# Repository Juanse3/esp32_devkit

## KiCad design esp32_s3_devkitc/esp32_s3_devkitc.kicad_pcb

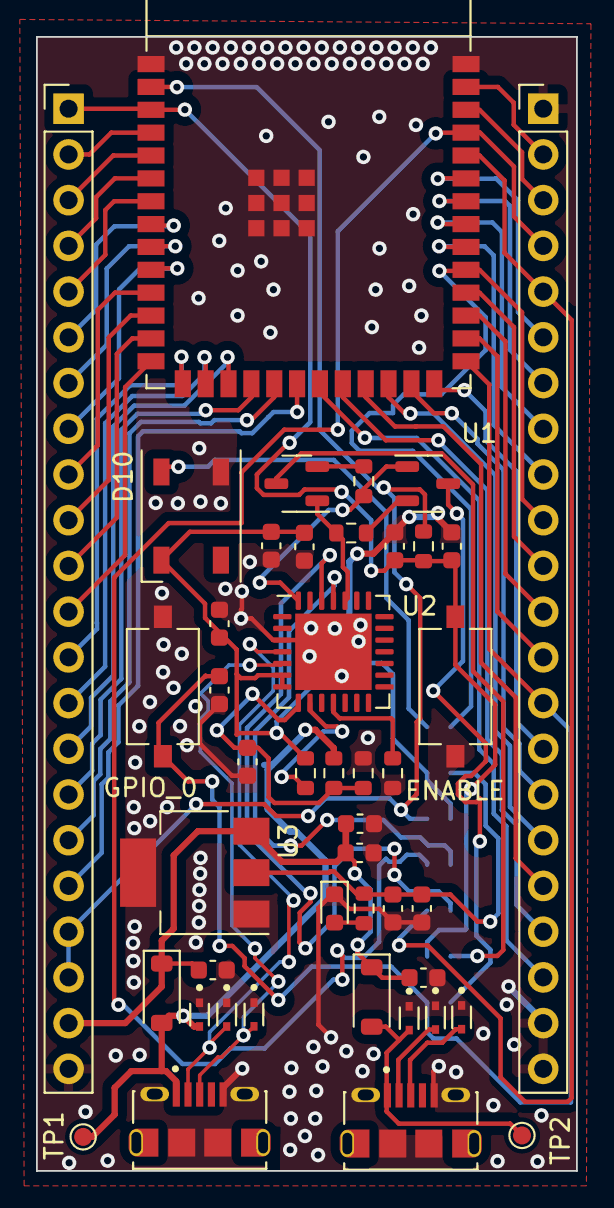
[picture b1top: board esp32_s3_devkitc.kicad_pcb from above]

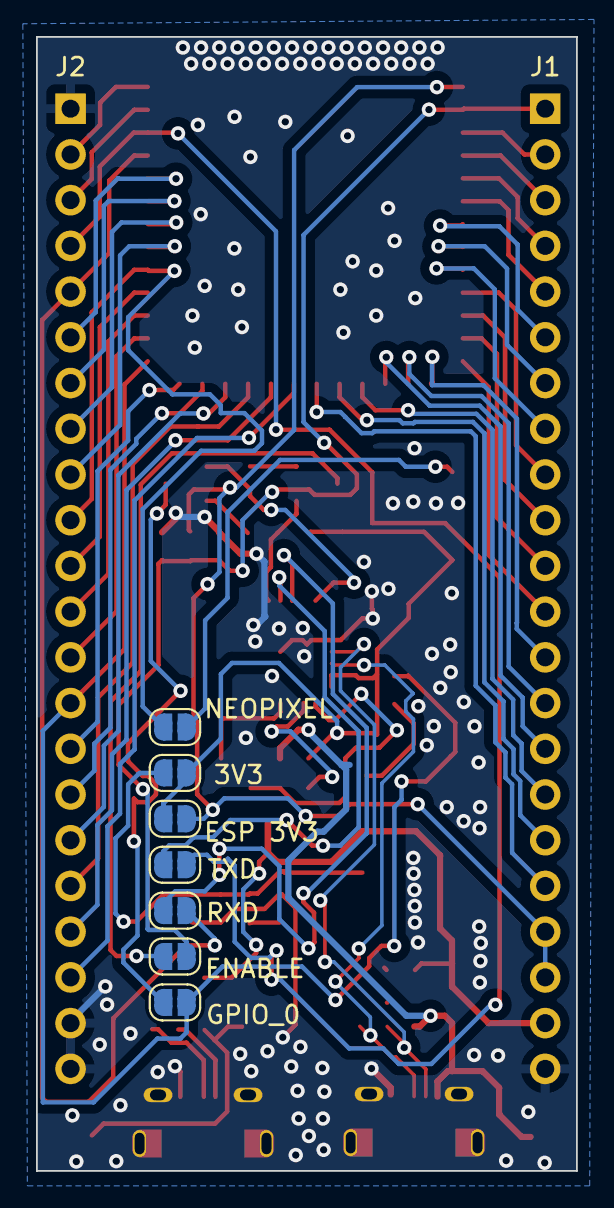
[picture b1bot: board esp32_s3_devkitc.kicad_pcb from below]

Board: 2 copper layers, 30.0 x 63.0 mm, 51 parts (7 on the bottom side), 61 nets.

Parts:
C1: 1uF/16V 0603 10%; C_0603_1608Metric
C2, C3, C6, C9, C10: 10uF/25V 0603; C_0603_1608Metric
C4: 1uF/16V 0603; C_0603_1608Metric
C5: c="10uF/25V 0603"; C_0603_1608Metric
C7, C8, C12, C13: 0.1uF/50V 0603; C_0603_1608Metric
C11: 01uF/50V 0603; C_0603_1608Metric
D1, D5: 1N5819HW-7-F; D_SOD-123
D2, D3, D4, D6, D7, D8: LESD5D5.0CT1G; TVS_LESD5D5.0CT1G
D9: LED RED; LED_0603_1608Metric
D10: SK6812; LED_WS2812B_PLCC4_5.0x5.0mm_P3.2mm
ENABLE: SW_Omron_B3FS; SW_Tactile_SPST_NO_Straight_CK_PTS636Sx25SMTRLFS
GPIO_0: SW_Omron_B3FS; SW_Tactile_SPST_NO_Straight_CK_PTS636Sx25SMTRLFS
J1, J2: Conn_01x22; PinHeader_1x22_P2.54mm_Vertical
J3: Micro USB (UART); AMPHENOL_10118194-0001LF
J4: Micro USB (NATIVE USB); AMPHENOL_10118194-0001LF
JP1: ENABLE; SolderJumper-2_P1.3mm_Open_RoundedPad1.0x1.5mm
JP2: GPIO_0; SolderJumper-2_P1.3mm_Open_RoundedPad1.0x1.5mm
JP3: RXD; SolderJumper-2_P1.3mm_Open_RoundedPad1.0x1.5mm
JP4: TXD; SolderJumper-2_P1.3mm_Open_RoundedPad1.0x1.5mm
JP5: NEOPIXEL; SolderJumper-2_P1.3mm_Open_RoundedPad1.0x1.5mm
JP6: 3V3; SolderJumper-2_P1.3mm_Open_RoundedPad1.0x1.5mm
JP7: ESP 3V3; SolderJumper-2_P1.3mm_Open_RoundedPad1.0x1.5mm
Q1, Q2: L8050QLT1G; SOT-23-3
R1, R2, R3, R7: 10K 0603 1%; R_0603_1608Metric
R4: 1K 0603 1%; R_0603_1608Metric
R5: 22.1K 0603 1%; R_0603_1608Metric
R6: 47.5K 0603 1%; R_0603_1608Metric
R9: 5.1K 0603 1%; R_0603_1608Metric
TP1: VBUS; TestPoint_Pad_D1.0mm
TP2: VBUSB; TestPoint_Pad_D1.0mm
U1: ESP32-S3-WROOM-1
U2: CP2102N-Axx-xQFN28; QFN-28-1EP_6x6mm_P0.65mm_EP4.25x4.25mm
U3: SGM2212-3.3; SOT-223

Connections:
/bridge-uart/DTR: Q2.1 (E), R1.1, U2.28 (~DTR)
/bridge-uart/GPIO_19: D7.2 (A2), J4.3 (D+)
/bridge-uart/GPIO_20: D8.2 (A2), J4.2 (D-)
/bridge-uart/RTS: Q1.1 (E), R2.1, U2.24 (~RTS)
/bridge-uart/U0RXD: J2.5, JP3.2 (B), U1.36 (U0RXD/GPIO44/CLK_OUT2)
/bridge-uart/U0TXD: J2.4, JP4.2 (B), U1.37 (U0TXD/GPIO43/CLK_OUT1)
/bridge-uart/USB_DN: D3.2 (A2), J3.3 (D+), U2.5 (D-)
/bridge-uart/USB_DP: D4.2 (A2), J3.2 (D-), U2.4 (D+)
/bridge-uart/VBUS: D1.2 (A), D2.2 (A2), J3.1 (VBUS), R5.1, TP1.1
/bridge-uart/VCC_3V3: C2.2, C10.1, C11.1, D10.3 (VDD), JP6.2 (B), JP7.1 (A), R4.1, U2.6 (VDD), U2.7 (VREGIN)
/bridge-uart/VCC_5V: C3.1, C5.1, C6.1, C7.1, D1.1 (K), D5.1 (K), J1.21, U3.3 (VI)
/btn+led/EN: C1.1, C13.1, ENABLE.2, J1.1, JP1.2 (B), R3.2, U1.3 (EN)
/btn+led/GPIO_38: J2.10, JP5.1 (A), U1.31 (GPIO38/FSPIWP/SUBSPIWP)
/esp32/ESP_3V3: J1.19, J1.20, JP7.2 (B), R3.1, U1.2 (3V3)
/esp32/GPIO_0: C12.1, GPIO_0.2, J2.14, JP2.2 (B), U1.27 (GPIO0/BOOT)
/esp32/GPIO_1: J2.2, U1.39 (GPIO1/TOUCH1/ADC1_CH0)
/esp32/GPIO_2: J2.3, U1.38 (GPIO2/TOUCH2/ADC1_CH1)
/esp32/GPIO_3: J1.13, U1.15 (GPIO3/TOUCH3/ADC1_CH2)
/esp32/GPIO_4: J1.2, U1.4 (GPIO4/TOUCH4/ADC1_CH3)
/esp32/GPIO_5: J1.3, U1.5 (GPIO5/TOUCH5/ADC1_CH4)
/esp32/GPIO_6: J1.4, U1.6 (GPIO6/TOUCH6/ADC1_CH5)
/esp32/GPIO_7: J1.5, U1.7 (GPIO7/TOUCH7/ADC1_CH6)
/esp32/GPIO_8: J1.10, U1.12 (GPIO8/TOUCH8/ADC1_CH7/SUBSPICS1)
/esp32/GPIO_9: J1.15, U1.17 (GPIO9/TOUCH9/ADC1_CH8/FSPIHD/SUBSPIHD)
/esp32/GPIO_10: J1.16, U1.18 (GPIO10/TOUCH10/ADC1_CH9/FSPICS0/FSPIIO4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)
/esp32/GPIO_11: J1.17, U1.19 (GPIO11/TOUCH11/ADC2_CH0/FSPID/FSPIIO5/S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)
/esp32/GPIO_12: J1.18, U1.20 (GPIO12/TOUCH12/ADC2_CH1/FSPICLK/FSPIIO6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)
/esp32/GPIO_13: J2.20, U1.21 (GPIO13/TOUCH13/ADC2_CH2/FSPIQ/FSPIIO7/S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)
/esp32/GPIO_14: J2.19, U1.22 (GPIO14/TOUCH14/ADC2_CH3/FSPIWP/FSPIDQS/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)
/esp32/GPIO_15: J1.6, U1.8 (GPIO15/U0RTS/ADC2_CH4/XTAL_32K_P)
/esp32/GPIO_16: J1.7, U1.9 (GPIO16/U0CTS/ADC2_CH5/XTAL_32K_N)
/esp32/GPIO_17: J1.8, U1.10 (GPIO17/U1TXD/ADC2_CH6)
/esp32/GPIO_18: J1.9, U1.11 (GPIO18/U1RXD/ADC2_CH7/CLK_OUT3)
/esp32/GPIO_19: J1.11, U1.13 (GPIO19/U1RTS/ADC2_CH8/CLK_OUT2/USB_D-)
/esp32/GPIO_20: J1.12, U1.14 (GPIO20/U1CTS/ADC2_CH9/CLK_OUT1/USB_D+)
/esp32/GPIO_21: J2.18, U1.23 (GPIO21)
/esp32/GPIO_35: J2.13, U1.28 (SPIIO6/GPIO35/FSPID/SUBSPID)
/esp32/GPIO_36: J2.12, U1.29 (SPIIO7/GPIO36/FSPICLK/SUBSPICLK)
/esp32/GPIO_37: J2.11, U1.30 (SPIDQS/GPIO37/FSPIQ/SUBSPIQ)
/esp32/GPIO_39: J2.9, U1.32 (MTCK/GPIO39/CLK_OUT3/SUBSPICS1)
/esp32/GPIO_40: J2.8, U1.33 (MTDO/GPIO40/CLK_OUT2)
/esp32/GPIO_41: J2.7, U1.34 (MTDI/GPIO41/CLK_OUT1)
/esp32/GPIO_42: J2.6, U1.35 (MTMS/GPIO42)
/esp32/GPIO_45: J2.15, U1.26 (GPIO45)
/esp32/GPIO_46: J1.14, U1.16 (GPIO46)
/esp32/GPIO_47: J2.17, U1.24 (GPIO47/SPICLK_P/SUBSPICLK_P_DIFF)
/esp32/GPIO_48: J2.16, U1.25 (GPIO48/SPICLK_N/SUBSPICLK_N_DIFF)
GND: C1.2, C2.1, C3.2, C4.2, C5.2, C6.2, C7.2, C8.2, C9.2, C10.2, C11.2, C12.2, C13.2, D2.1 (A1), D3.1 (A1), D4.1 (A1), D6.1 (A1), D7.1 (A1), D8.1 (A1), D9.1 (K), D10.1 (VSS), ENABLE.1, GPIO_0.1, J1.22, J2.1, J2.21, J2.22, J3.5 (GND), J3.S1, J3.S2, J3.S3, J3.S4, J3.S5, J3.S6, J4.5 (GND), J4.S1, J4.S2, J4.S3, J4.S4, J4.S5, J4.S6, R6.2, R7.2, U1.1 (GND), U1.40 (GND), U1.41 (GND), U2.3 (GND), U2.29 (GND), U3.1 (GND), U3.4
unnamed: D5.2 (A), D6.2 (A2), J4.1 (VBUS), TP2.1
unnamed: D9.2 (A), R9.2
unnamed: D10.2 (DIN), JP5.2 (B)
unnamed: JP1.1 (A), Q1.3 (C)
unnamed: JP2.1 (A), Q2.3 (C)
unnamed: JP3.1 (A), U2.26 (TXD)
unnamed: JP4.1 (A), U2.25 (RXD)
unnamed: C8.1, C9.1, JP6.1 (A), R9.1, U3.2 (VO)
unnamed: Q1.2 (B), R1.2
unnamed: Q2.2 (B), R2.2
unnamed: C4.1, R5.2, R6.1, U2.8 (VBUS)
unnamed: R4.2, U2.9 (~RST)
unnamed: R7.1, U2.11 (~SUSPEND)

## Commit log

2023-11-17 fix de componentes desconectados y reodenamiento de vias
